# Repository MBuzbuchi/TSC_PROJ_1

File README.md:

# TSC_PROJ_1

E_Book proj

# _**Bloc Scheme**_

# _**Description of Hardware Functionality**_

Below is an extended list of the hardware components identified in the schematic, along with each component’s role and functionality, 
plus some operational details. These explanations help clarify how the entire system is built and why these design choices were made.

## 1. USB-C Connector & ESD Protection

### Key Components
- **USBLC6-2SC6Y** – TVS (Transient Voltage Suppressor) diode specialized for USB data line protection.  
  - **Approx. Price**: \$0.10–\$0.30 (single unit)  
- **PFMF.050.1** – resettable fuse (PTC) protecting the power line from excessive current.  
  - **Approx. Price**: \$0.10–\$0.20  
- **R2-USB1 / R2-USB** (5 kΩ) – matching/termination resistors on the USB D+ and D– data lines.  
  - **Approx. Price**: \$0.01–\$0.02 each  

### Function
- The USB-C connector supplies both power (5 V) to the system and USB data connectivity.  
- The ESD protection diode safeguards the USB data lines from electrostatic discharges up to several kV, maintaining the integrity of the data signals and internal converters.  
- The PTC fuse automatically resets once the current drops, preventing damage when short circuits or overcurrent situations occur on the USB port.

### Operational Data
- 5 V power supply from the USB, typically up to 500 mA (USB 2.0), or more depending on the USB-C source.  
- Data transfer rates up to 480 Mbps (USB 2.0 High Speed).

---

## 2. Voltage Regulators (LDO Voltage Regulator)

### Key Components
- **XC6220A331MR-G** – an LDO (Low Dropout) regulator delivering a stable 3.3 V output.  
  - **Approx. Price**: \$0.20–\$0.50  
- **DMG2305UX-7** – P-channel MOSFET used for power switching (possibly for reverse voltage protection or for reducing quiescent current when switching between USB and battery power).  
  - **Approx. Price**: \$0.10–\$0.30  

### Function
- Provides a constant 3.3 V rail for powering the ESP32-C6 and other logic circuits/sensors.  
- Can also serve as an additional protection stage, keeping the supply stable and filtering noise that may come from the USB source.

### Operational Data
- Input voltage range: ~3.5 V to 5.5 V (according to the LDO specs).  
- Output current up to ~300 mA.  
- Built-in overcurrent and thermal shutdown protection, ensuring circuit safety.

---

## 3. Li-Po Charging Controller (MCP73831/73832)

### Key Component
- **MCP73831** – a simple charge-management IC, configurable by an external resistor (PROG) to set the charge current.  
  - **Approx. Price**: \$0.50–\$0.80  

### Function
- Safely charges a single-cell Li-Po battery, regulating up to 4.2 V and controlling a maximum charge current.  
- Integrates temperature monitoring (via external NTC or dedicated resistor), charge status indicator (LED), and automatically switches to a float maintenance mode once the battery is fully charged.

### Operational Data
- Typically powered by a 5 V USB input.  
- Charge current (set by the PROG resistor) – e.g., 100 mA, 500 mA, etc., depending on the battery requirements.  
- Over-voltage, over-temperature, and short-circuit protection.

---

## 4. Single-Cell Li-Po Battery

### Function
- Stores electrical energy to power the device, enabling operation without a continuous USB supply.

### Operational Data
- Nominal voltage of ~3.7 V, fully charged at 4.2 V.  
- Capacity depends on the specific battery (500 mAh, 1000 mAh, etc.), which affects run time.  
- **Approx. Price**: Ranges from \$3 to \$8 or more, depending on capacity/brand.

---

## 5. ESP32-C6 Microcontroller (ESP32-C6-WROOM-1-N8)

### Function
- Core processing unit, running firmware and handling wireless communication (Wi-Fi 6, Bluetooth LE), as well as peripheral interfaces (SPI, I2C, UART, GPIO).  
- Integrates a 160 MHz RISC-V CPU, onboard Flash, SRAM, and hardware security features.

### Operational Data
- Powered at 3.3 V.  
- Low-power modes for efficient battery operation, ideal for portable IoT applications.  
- Interfaces with the E-Paper display (SPI), SD card (SPI), BME688 sensor (I2C), DS3231 RTC (I2C), and MAX17048 fuel gauge (I2C).  
- **Approx. Price**: \$2.50–\$5.00 (depending on memory size and supplier)

---

## 6. SD Card Interface

### Key Components
- MicroSD socket with card detection pins (CD, DETECTION_1, DETECTION_2).  
  - **Approx. Price**: \$0.40–\$1.00

### Function
- Provides a removable storage option for logging data, configuration files, E-Paper images, etc.  
- Uses SPI lines (SCK, MISO, MOSI, SS_SD) for communication with the ESP32-C6.

### Operational Data
- Operates at 3.3 V.  
- Supports SD/SDHC cards up to multiple GB, depending on firmware support.
- SD card itself (not included in the socket cost) can range from \$3 to \$20+ depending on capacity and speed class.

---

## 7. E-Paper Drive Circuit

### Key Components
- **MBR0530** Schottky diodes (e.g., D3, D4, D5) for protection and rectification in the voltage-boosting section.  
  - **Approx. Price**: \$0.05–\$0.10 each  
- **Inductor L1** (68 µH) for boost converter operation.  
  - **Approx. Price**: \$0.10–\$0.30 (depends on current rating)  
- **SI1308EDL-T1-GE3** MOSFET for switching in the high-voltage generator.  
  - **Approx. Price**: \$0.15–\$0.30  

### Function
- Creates the specialized positive and negative voltages (EPD_VGH, EPD_VGL) required by the E-Paper display.  
- Converts 3.3 V into higher and/or negative voltages needed to update the E-Ink display.

### Operational Data
- Typical output ranges: +15…22 V and -15…22 V (depending on the specific panel).  
- MBR0530 diodes have a low forward drop and can handle relatively high currents for this type of circuit.

---

## 8. Display Type Selector

### Key Components
- Jumper **SJ1**, resistor **R2** (2.2 kΩ).  
  - **Approx. Price**: Jumper \$0.05–\$0.10, resistor \$0.01–\$0.02

### Function
- Allows configuration of control pins (e.g. **RES**, **BUSY**) or power lines to support various E-Paper panel types.  
- Moving the jumper can route or enable certain lines depending on the display’s requirements.

---

## 9. E-Paper Display Header

### Component
- FFC (Flat Flex Cable) connector, **FH34SRJ-24S-0.5SH** (24-pin) or similar.  
  - **Approx. Price**: \$0.40–\$0.80

### Function
- A mechanical and electrical interface between the main board and the E-Paper module.  
- Includes SPI signals (SCK, MOSI, MISO—if bi-directional), control signals (CS, DC), reset line (RES), busy line (BUSY), and power lines (3.3 V, GND, EPD_VGH, EPD_VGL).

---

## 10. Battery Fuel Gauge (MAX17048)

### Key Component
- **MAX17048G+T10** – Fuel gauge with an I²C interface.  
  - **Approx. Price**: \$1.20–\$2.00

### Function
- Measures the Li-Po battery voltage and estimates its state of charge (SOC) in real time, compensating for temperature and discharge characteristics.  
- Allows the microcontroller to display battery level and react to critical low-battery states.

### Operational Data
- I²C interface at 3.3 V.  
- ±1–2% SOC accuracy.  
- Configurable alert output for low battery.

---

## 11. External Flash Memory (W25Q512JVEIQ, 64MB)

### Function
- Additional non-volatile storage (up to 64Mb or 512Mbit, i.e. 8 MB, depending on suffix) for images, fonts, configuration files, and Over-the-Air (OTA) firmware updates.

### Operational Data
- SPI interface with speeds up to 133 MHz.  
- 3.3 V supply voltage.  
- Up to 100,000 write/erase cycles and 20-year data retention.  
- **Approx. Price**: \$1.50–\$3.00 (depending on density and supplier)

---

## 12. SPI ESD Protection Lines

### Key Components
- **PGB1010603MR** (Polymeric ESD Suppressor) and 10 kΩ series resistors.  
  - **Approx. Price**: \$0.05–\$0.15 each for the suppressors, \$0.01 for each resistor

### Function
- Protects SPI data lines from electrostatic discharges, which can occur when plugging in peripherals or when the lines are touched without proper handling.  
- The 10 kΩ resistors help limit transient current before it reaches the TVS diode, providing additional filtering.

### Operational Data
- ESD protection up to ±8 kV (contact discharge).

---

## 13. Qwiic / Stemma QT Connector (I2C)

### Component
- 4-pin connector (GND, 3.3 V, SDA, SCL).  
  - **Approx. Price**: \$0.30–\$0.60

### Function
- Provides a standardized, plug-and-play interface for quickly adding I2C-based sensors or other modules.

### Operational Data
- Compatible with SparkFun Qwiic and Adafruit Stemma QT systems.  
- 3.3 V supply voltage.

---

## 14. RTC Module (DS3231SN)

### Key Component
- **DS3231SN** – A high-accuracy real-time clock with an integrated temperature-compensated oscillator (TCXO).  
  - **Approx. Price**: \$1.50–\$3.00

### Function
- Maintains precise timekeeping with minimal drift (±2 ppm, equivalent to ±1 minute/year in some conditions).  
- Communicates with the microcontroller via I²C for automatic time syncing.  
- Can keep time even when main power is off, using a backup battery on VBAT.

### Operational Data
- 3.3 V supply voltage.  
- Operating temperature range from -40 °C to +85 °C (depending on the specific version).

---

## 15. Test Pads

### Component
- Test points (TP1…TP17) placed around the PCB.  
  - **Approx. Price**: Usually negligible (just copper pads), sometimes \$0.01–\$0.02 each if you count plating cost.

### Function
- Provide direct access to key signals (SPI, I2C, GPIO) for debugging, measurements, programming, or firmware updates.  
- Highly useful for prototyping, quality control, and mass production validation.

---

# _**Bill of Materials**_
Data sheets and links to websites were included only at the first mention of components that appear multiple times in the project. Components such as test points (TP), do not have tehnical description or present a data sheet because these were designed personally

| Name of component  | Device                                    | Check Prices                                                                 | DataSheet                                                                  |
|--------------------|-------------------------------------------|-----------------------------------------------------------------------------|----------------------------------------------------------------------------|
| BOOT_BUTTON        | BUTTON_CUSYOMV1                           | [Check Price](https://industry.panasonic.com/global/en/products/control/switch/light-touch/number/evqpuj02k)  | [DataSheet](https://industry.panasonic.com/global/en/products/control/switch/light-touch/number/evqpuj02k) |
| C1                 | ESP32_WROVER_EAGLE-LTSPICE_CC0402         | [Check Price](https://industry.panasonic.com/global/en/products/control/switch/light-touch/number/evqpuj02k)  | [DataSheet](https://industry.panasonic.com/global/en/products/control/switch/light-touch/number/evqpuj02k) |
| C1_BAT             | ESP32_WROVER_EAGLE-LTSPICE_CC0402         | #N/A                                                                         | #N/A                                                                      |
| C1_BAT1            | EAGLE-LTSPICE_CC0402                      | #N/A                                                                         | #N/A                                                                      |
| C1_BAT2            | EAGLE-LTSPICE_CC0402                      | #N/A                                                                         | #N/A                                                                      |
| C2                 | ESP32_WROVER_EAGLE-LTSPICE_CC0402         | #N/A                                                                         | #N/A                                                                      |
| C2_BAT\            | ESP32_WROVER_EAGLE-LTSPICE_CC0402         | #N/A                                                                         | #N/A                                                                      |
| C3                 | RCL_CPOL-EUCT3528                         | #N/A                                                                         | #N/A                                                                      |
| C4                 | ESP32_WROVER_EAGLE-LTSPICE_CC0402         | #N/A                                                                         | #N/A                                                                      |
| C4_USB             | ESP32_WROVER_EAGLE-LTSPICE_CC0402         | #N/A                                                                         | #N/A                                                                      |
| C5                 | ESP32_WROVER_EAGLE-LTSPICE_CC0402         | #N/A                                                                         | #N/A                                                                      |
| C5_USB             | ESP32_WROVER_EAGLE-LTSPICE_CC0402         | #N/A                                                                         | #N/A                                                                      |
| C6                 | ESP32_WROVER_EAGLE-LTSPICE_CC0402         | #N/A                                                                         | #N/A                                                                      |
| C7                 | ESP32_WROVER_EAGLE-LTSPICE_CC0402         | #N/A                                                                         | #N/A                                                                      |
| C8                 | ESP32_WROVER_EAGLE-LTSPICE_CC0402         | #N/A                                                                         | #N/A                                                                      |
| C9                 | EAGLE-LTSPICE_CC0402                      | #N/A                                                                         | #N/A                                                                      |
| C10                | ESP32_WROVER_EAGLE-LTSPICE_CC0402         | #N/A                                                                         | #N/A                                                                      |
| C10_SUPERCAP       | CPH3225A                                  | [Check Price](https://www.snapeda.com/parts/CPH3225A/Seiko+Instruments/view-part/?ref=eda) | [DataSheet](https://www.snapeda.com/parts/CPH3225A/Seiko+Instruments/view-part/?ref=eda) |
| CHANGE_BUTTON      | BUTTON_CUSYOMV1                           | [Check Price](https://industry.panasonic.com/global/en/products/control/switch-light-touch/number/evqpuj02k)  | [DataSheet](https://industry.panasonic.com/global/en/products/control/switch-light-touch/number/evqpuj02k) |
| CHG_LED            | ADAFRUIT_LEDCHIP-LED0603                  | [Check Price](https://www.snapeda.com/parts/KP-1608SURCK/Kingbright/view-part/?ref=search&t=LED%200603) | [DataSheet](https://www.snapeda.com/parts/KP-1608SURCK/Kingbright/view-part/?ref=search&t=LED%200603) |
| C_DELAY            | ESP32_WROVER_EAGLE-LTSPICE_CC0402         | #N/A                                                                         | #N/A                                                                      |
| D1                 | USBLC6-2SC6Y                              | [Check Price](https://www.snapeda.com/parts/USBLC6-2SC6Y/STMicroelectronics/view-part/?ref=eda) | [DataSheet](https://www.snapeda.com/parts/USBLC6-2SC6Y/STMicroelectronics/view-part/?ref=eda) |
| D2                 | ESP32_WROVER_AVX---SD0805S020S1R0_AVX_... | [Check Price](https://eu.mouser.com/ProductDetail/KYOCERA-AVX/SD0805S020S1R0?qs=jCA%252BPfw4LHbpkAoSnwrdjw%3D%3D) | [DataSheet](http://datasheets.avx.com/schottky.pdf)                       |
| D3                 | MBR0530                                   | [Check Price](https://eu.mouser.com/ProductDetail/KYOCERA-AVX/SD0805S020S1R0?qs=jCA%252BPfw4LHbpkAoSnwrdjw%3D%3D) | [DataSheet](https://eu.mouser.com/ProductDetail/KYOCERA-AVX/SD0805S020S1R0?qs=jCA%252BPfw4LHbpkAoSnwrdjw%3D%3D) |
| D4                 | MBR0530                                   | [Check Price](https://www.snapeda.com/parts/MBR0530/Onsemi/view-part/?ref=eda) | [DataSheet](https://www.snapeda.com/parts/MBR0530/Onsemi/view-part/?ref=eda) |
| D5                 | MBR0530                                   | [Check Price](https://www.snapeda.com/parts/MBR0530/Onsemi/view-part/?ref=eda) | [DataSheet](https://www.snapeda.com/parts/MBR0530/Onsemi/view-part/?ref=eda) |
| D6                 | PGB1010603MR                              | [Check Price](https://www.snapeda.com/parts/PGB1010603MR/Littelfuse/view-part/?ref=eda) | [DataSheet](https://www.snapeda.com/parts/PGB1010603MR/Littelfuse/view-part/?ref=eda) |
| D7                 | ESP32_WROVER_AVX---SD0805S020S1R0_AVX_... | [Check Price](https://eu.mouser.com/ProductDetail/KYOCERA-AVX/SD0805S020S1R0?qs=jCA%252BPfw4LHbpkAoSnwrdjw%3D%3D) | [DataSheet](http://datasheets.avx.com/schottky.pdf)                       |
| D8                 | PGB1010603MR                              | [Check Price](https://www.snapeda.com/parts/PGB1010603MR/Littelfuse/view-part/?ref=eda) | [DataSheet](https://www.snapeda.com/parts/PGB1010603MR/Littelfuse/view-part/?ref=eda) |
| D9                 | PGB1010603MR                              | [Check Price](https://www.snapeda.com/parts/PGB1010603MR/Littelfuse/view-part/?ref=eda) | [DataSheet](https://www.snapeda.com/parts/PGB1010603MR/Littelfuse/view-part/?ref=eda) |
| D10                | PGB1010603MR                              | [Check Price](https://www.snapeda.com/parts/PGB1010603MR/Littelfuse/view-part/?ref=eda) | [DataSheet](https://www.snapeda.com/parts/PGB1010603MR/Littelfuse/view-part/?ref=eda) |
| D11                | PGB1010603MR                              | [Check Price](https://www.snapeda.com/parts/PGB1010603MR/Littelfuse/view-part/?ref=eda) | [DataSheet](https://www.snapeda.com/parts/PGB1010603MR/Littelfuse/view-part/?ref=eda) |
| D12                | PGB1010603MR                              | [Check Price](https://www.snapeda.com/parts/PGB1010603MR/Littelfuse/view-part/?ref=eda) | [DataSheet](https://www.snapeda.com/parts/PGB1010603MR/Littelfuse/view-part/?ref=eda) |
| EPD_C1             | ESP32_WROVER_EAGLE-LTSPICE_CC0402         | #N/A                                                                         | #N/A                                                                      |
| EPD_C2             | ESP32_WROVER_EAGLE-LTSPICE_CC0402         | #N/A                                                                         | #N/A                                                                      |
| EPD_C5             | ESP32_WROVER_EAGLE-LTSPICE_CC0402         | #N/A                                                                         | #N/A                                                                      |
| EPD_C6             | ESP32_WROVER_EAGLE-LTSPICE_CC0402         | #N/A                                                                         | #N/A                                                                      |
| EPD_C7             | ESP32_WROVER_EAGLE-LTSPICE_CC0402         | #N/A                                                                         | #N/A                                                                      |
| EPD_C8             | ESP32_WROVER_EAGLE-LTSPICE_CC0402         | #N/A                                                                         | #N/A                                                                      |
| EPD_C9             | ESP32_WROVER_EAGLE-LTSPICE_CC0402         | #N/A                                                                         | #N/A                                                                      |
| EPD_C10            | ESP32_WROVER_EAGLE-LTSPICE_CC0402         | #N/A                                                                         | #N/A                                                                      |
| EPD_C11            | ESP32_WROVER_EAGLE-LTSPICE_CC0402         | #N/A                                                                         | #N/A                                                                      |
| EPD_C12            | ESP32_WROVER_EAGLE-LTSPICE_CC0402         | #N/A                                                                         | #N/A                                                                      |
| IC1                | BD5229G-TR                                | [Check Price](https://componentsearchengine.com/part-view/BD5229G-TR/ROHM%20Semiconductor) | [DataSheet](https://componentsearchengine.com/part-view/BD5229G-TR/ROHM%20Semiconductor) |
| IC4                | XC6220A331MR-G                            | [Check Price](https://componentsearchengine.com/part-view/XC6220A331MR-G/Torex) | [DataSheet](https://componentsearchengine.com/part-view/XC6220A331MR-G/Torex) |
| J1                 | FH34SRJ-24S-0.5SH_99_                     | [Check Price](https://componentsearchengine.com/part-view/XC6220A331MR-G/Torex) | [DataSheet](https://componentsearchengine.com/part-view/XC6220A331MR-G/Torex) |
| J2                 | SAMACSYS_PARTS_USB4110-GF-A               | [Check Price](https://componentsearchengine.com/part-view/USB4110-GF-A/GCT%20(GLOBAL%20CONNECTOR%20TECHNOLOGY) | [DataSheet](https://componentsearchengine.com/part-view/USB4110-GF-A/GCT%20(GLOBAL%20CONNECTOR%20TECHNOLOGY) |
| J3                 | QWIIC_CONNECTORJS-1MM                     | #N/A                                                                         | #N/A                                                                      |
| J4                 | 112A-TAAR-R03_ATTEND                      | [Check Price](https://store.comet.srl.ro/Catalogue/Product/43497/)           | [DataSheet](https://store.comet.srl.ro/Catalogue/Product/43497/)          |
| L1                 | 744043680IND_4828-WE-TPC_WRE              | [Check Price](https://eu.mouser.com/ProductDetail/Wurth-Elektronik/744043680?qs=PGXP4M47uW6VkZq%252BkzjrHA%3D%3D) | [DataSheet](https://eu.mouser.com/ProductDetail/Wurth-Elektronik/744043680?qs=PGXP4M47uW6VkZq%252BkzjrHA%3D%3D) |
| PFMF.050.1         | ESP32C6_VARISTORCN1812                    | [Check Price](https://www.mouser.co.uk/ProductDetail/EPCOS-TDK/B72520T0350K062?qs=dEfas%2FXlABIszF52uu7vrg%3D%3D) | [DataSheet](https://www.mouser.co.uk/ProductDetail/EPCOS-TDK/B72520T0350K062?qs=dEfas%2FXlABIszF52uu7vrg%3D%3D) |
| Q1                 | ESP32_WROVER_SPARKFUN-DISCRETESEMI_MOSFET_... | [Check Price](https://componentsearchengine.com/part-view/DMG2305UX-7/Diodes%20Incorporated) | [DataSheet](https://componentsearchengine.com/part-view/DMG2305UX-7/Diodes%20Incorporated) |
| Q2                 | ESP32_WROVER_SPARKFUN-DISCRETESEMI_MOSFET_... | #N/A                                                                         | #N/A                                                                      |
| Q3                 | D8                                        | [Check Price](https://componentsearchengine.com/part-view/PGB1010603MR/Littelfuse) | [DataSheet](https://componentsearchengine.com/part-view/PGB1010603MR/Littelfuse) |
| Q4                 | Q2_TS-B2_REACHPACK                        | #N/A                                                                         | #N/A                                                                      |

# _**Pin Allocation for ESP32-C6**_

| Pin ESP32-C6  | Componentă / Semnal                       | Explicație                                           |
|---------------|-------------------------------------------|------------------------------------------------------|
| GPIO1         | I²C SDA (BME688, MAX17048, DS3231, Qwiic) | Se folosește pentru a partaja magistrala I²C între toți senzorii și RTC. |
| GPIO2         | I²C SCL (BME688, MAX17048, DS3231, Qwiic) | Linia de clock pentru comunicarea I²C.              |
| GPIO5         | SPI MISO (E-Paper)                       | Pinul pentru citirea datelor sau a statusului de la ecranul e-paper. |
| GPIO6         | SPI MOSI (E-Paper)                       | Trimiterea datelor către ecranul e-paper.            |
| GPIO7         | SPI CLK (E-Paper)                        | Semnal de clock pentru sincronizarea cu e-paper.    |
| GPIO8         | SPI CS (E-Paper)                         | Chip Select pentru a activa comunicarea cu e-paper.  |
| GPIO9         | E-Paper DC (Data/Command)                | Semnal pentru a diferenția între date și comenzi pentru ecranul e-paper. |
| GPIO10        | E-Paper RST                              | Pinul de reset hardware pentru e-paper.              |
| GPIO11        | E-Paper BUSY                             | Intrare din display care indică dacă ecranul este ocupat sau nu. |
| GPIO12        | Button #1                                | Intrare digitală pentru primul buton (ex. pagina următoare). |
| GPIO13        | Button #2                                | Intrare digitală pentru al doilea buton (ex. pagina anterioară). |
| GPIO14        | Button #3                                | Intrare digitală pentru al treilea buton (ex. Meniu/OK). |
| GPIO15        | MAX17048 ALERT (opțional)                | Semnal de alertă de la MAX17048 pentru nivel scăzut al bateriei. |
| GPIO16        | USB D+ (intern la USB PHY)               | Pin dedicat pentru semnalul USB 2.0 (D+).            |
| GPIO17        | USB D- (intern la USB PHY)               | Pin dedicat pentru semnalul USB 2.0 (D-).            |
| GPIO18        | LED de status (opțional)                 | Indicator pentru diverse stări (ex. Wi-Fi, încărcare, etc.). |
| GPIO19        | SD Card CS (opțional)                    | Chip Select pentru cardul SD (dacă se folosește SPI). |
| GPIO20        | SD Card MISO (opțional)                  | Intrare date de la cardul SD.                        |
| GPIO21        | SD Card MOSI (opțional)                  | Ieșire date către cardul SD.                         |
| GPIO4         | SD Card CLK (opțional)                   | Semnal de clock pentru cardul SD (SPI).              |

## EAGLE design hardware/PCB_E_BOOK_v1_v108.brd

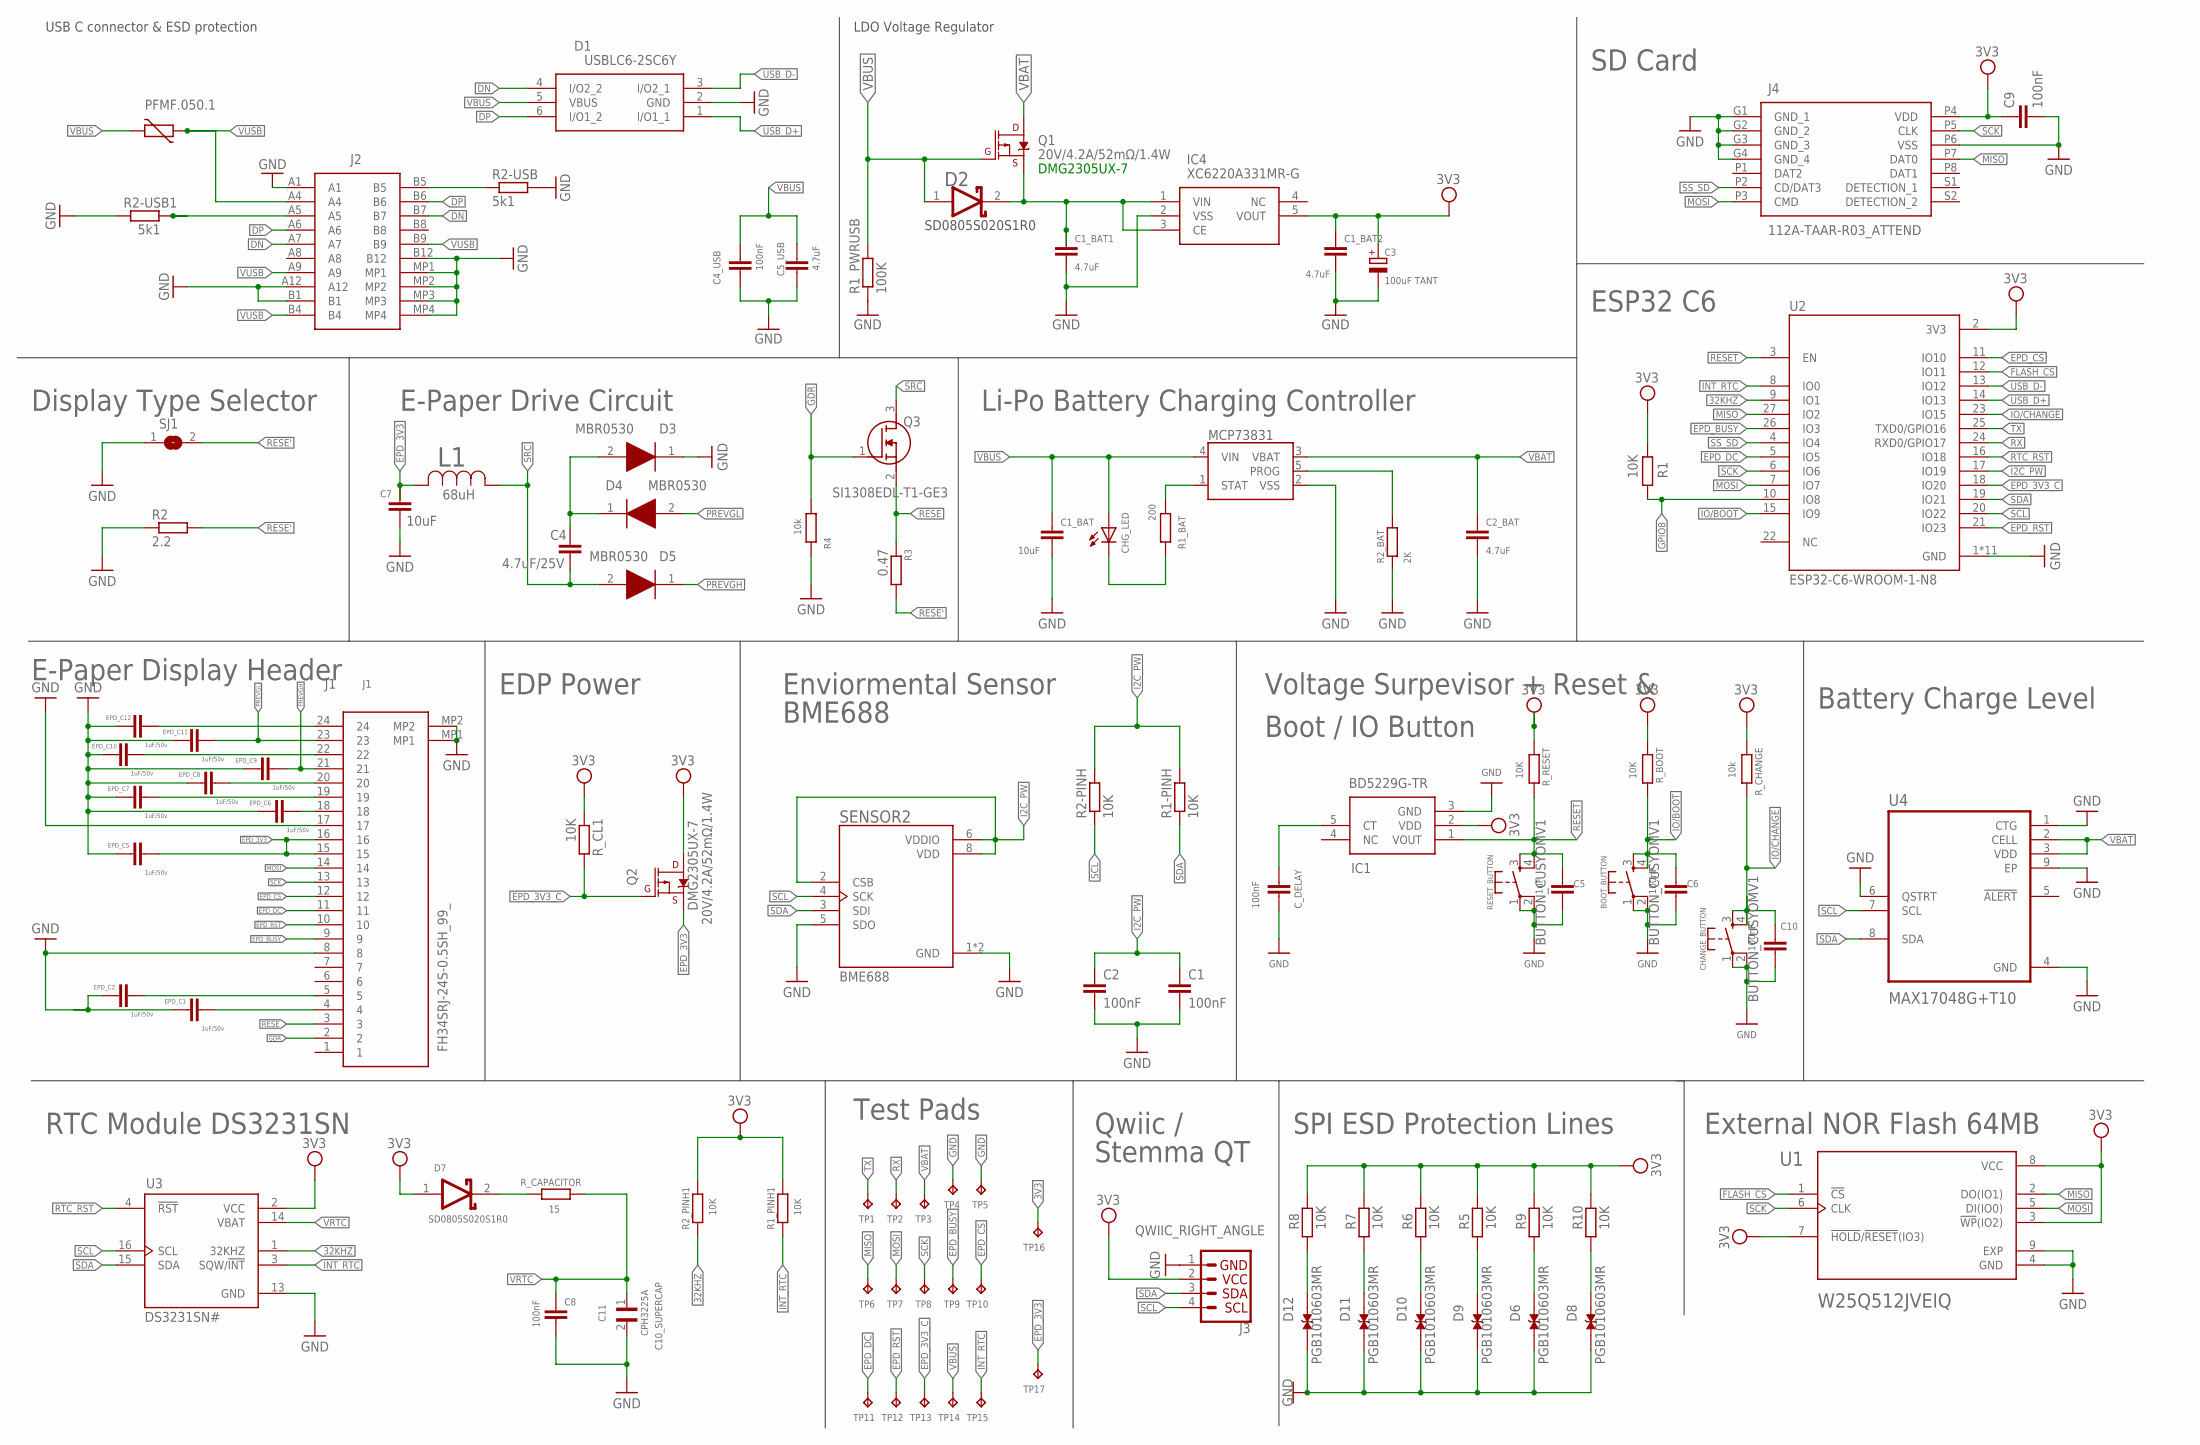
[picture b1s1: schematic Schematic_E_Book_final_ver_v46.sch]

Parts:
BOOT_BUTTON: BUTTON_CUSYOMV1; MYBUTTON
C1, C2, C4_USB, C6, C8, C9, C10: 100nF; EAGLE-LTSPICE_C0402
C1_BAT, C7: 10uF; EAGLE-LTSPICE_C0402
C1_BAT1, C1_BAT2, C2_BAT, C5_USB: 4.7uF; EAGLE-LTSPICE_C0402
C3: 100uF TANT; RCL_CT3528
C4: 4.7uF/25V; EAGLE-LTSPICE_C0402
C5: 1uF; EAGLE-LTSPICE_C0402
C11: CPH3225A; CAPCP3225X100N
CHANGE_BUTTON: BUTTON_CUSYOMV1; MYBUTTON
CHG_LED: ADAFRUIT_LEDCHIP-LED0603; ADAFRUIT_CHIP-LED0603
C_DELAY: 100nF; EAGLE-LTSPICE_C0402
D1: USBLC6-2SC6Y; SOT95P280X145-6N
D2: SD0805S020S1R0; ESP32_WROVER_AVX---SD0805S020S1R0_AVX_SD0805S020S1R0_0
D3, D4, D5: MBR0530; SOD3716X135N
D6, D8, D9, D10, D11, D12: PGB1010603MR; DIOC1608X36N
D7: ESP32_WROVER_AVX---SD0805S020S1R0_AVX_SD0805S020S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; ESP32_WROVER_AVX---SD0805S020S1R0_AVX_SD0805S020S1R0_0
EPD_C1, EPD_C2, EPD_C5, EPD_C6, EPD_C7, EPD_C8, EPD_C9, EPD_C10, EPD_C11, EPD_C12: 1uF/50v; EAGLE-LTSPICE_C0402
IC1: BD5229G-TR; SOT95P280X125-5N
IC4: XC6220A331MR-G; SOT95P280X120-5N
J1: FH34SRJ-24S-0.5SH_99_; FH34SRJ24S05SH99
J2: SAMACSYS_PARTS_USB4110-GF-A; SAMACSYS_PARTS_USB4110GFA
J3: QWIIC_RIGHT_ANGLE; JST04_1MM_RA
J4: 112A-TAAR-R03_ATTEND; 112ATAARR03ATTEND
L1: 68uH; IND_4828-WE-TPC_WRE
MCP73831: ESP32_WROVER_SPARKFUN-IC-POWER_MCP73831; ESP32_WROVER_SPARKFUN-IC-POWER_SOT23-5
PFMF.050.1: ESP32C6_VARISTORCN1812; ESP32C6_VARISTOR_CT/CN1812
Q1, Q2: 20V/4.2A/52mΩ/1.4W; ESP32_WROVER_SPARKFUN-DISCRETESEMI_SOT23-3
Q3: SI1308EDL-T1-GE3; SOT65P210X110-3N
R1, R1-PINH, R1_PINH1, R2-PINH, R2_PINH1, R5, R6, R7, R8, R9, R10: 10K; ESP32_WROVER_EAGLE-LTSPICE_R0402
R1_BAT: 200; ESP32_WROVER_EAGLE-LTSPICE_R0402
R1_PWRUSB: 100K; ESP32_WROVER_EAGLE-LTSPICE_R0402
R2: 2.2; ESP32_WROVER_EAGLE-LTSPICE_R0402
R2-USB, R2-USB1: 5k1; ESP32_WROVER_EAGLE-LTSPICE_R0402
R2_BAT: 2K; ESP32_WROVER_EAGLE-LTSPICE_R0402
R3: 0.47; ESP32_WROVER_EAGLE-LTSPICE_R0402
R4: 10k; ESP32_WROVER_EAGLE-LTSPICE_R0402
RESET_BUTTON: BUTTON_CUSYOMV1; MYBUTTON
R_BOOT: 10K; ESP32_WROVER_EAGLE-LTSPICE_R0402
R_CAPACITOR: 15; ESP32_WROVER_EAGLE-LTSPICE_R0402
R_CHANGE: 10k; ESP32_WROVER_EAGLE-LTSPICE_R0402
R_CL1: 10K; ESP32_WROVER_EAGLE-LTSPICE_R0402
R_RESET: 10K; ESP32_WROVER_EAGLE-LTSPICE_R0402
SENSOR2: ESP32_WROVER_BME680_BME680; ESP32_WROVER_BME680_PSON80P300X300X100-8N
SJ1: SJ
TP1, TP2, TP3, TP4, TP5, TP6, TP7, TP8, TP9, TP10, TP11, TP12, TP13, TP14, TP15, TP16, TP17: TPTP20R; TP20R
U1: W25Q512JVEIQ; SON127P600X800X80-9N
U2: ESP32-C6-WROOM-1-N8; XCVR_ESP32-C6-WROOM-1-N8
U3: DS3231SN#; SOIC127P1032X265-16N
U4: MAX17048G+T10; SON50P200X200X80-9N

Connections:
3V3: C1_BAT2.1, C3.+, C9.1, D7.1 (ANODE), IC1.2 (VDD), IC4.5 (VOUT), J3.2, J4.P4 (VDD), Q2.3 (D), R1.2, R1_PINH1.2, R2_PINH1.2, R5.2, R6.2, R7.2, R8.2, R9.2, R10.2, R_BOOT.1, R_CHANGE.1, R_CL1.1, R_RESET.1, TP16.TP, U1.3 (!WP!(IO2)), U1.7 (!HOLD!/!RESET!(IO3)), U1.8 (VCC), U2.2 (3V3), U3.2 (VCC)
32KHZ: R2_PINH1.1, U2.9 (IO1), U3.1 (32KHZ)
DN: D1.4 (I/O2_2), J2.A7, J2.B7
DP: D1.6 (I/O1_2), J2.A6, J2.B6
EPD_3V3: C7.1, EPD_C5.1, J1.15, J1.16, L1.2, Q2.2 (S), TP17.TP
EPD_3V3_C: Q2.1 (G), R_CL1.2, TP13.TP, U2.18 (IO20)
EPD_BUSY: J1.9, TP9.TP, U2.26 (IO3)
EPD_CS: J1.12, TP10.TP, U2.11 (IO10)
EPD_DC: J1.11, TP11.TP, U2.5 (IO5)
EPD_RST: J1.10, TP12.TP, U2.21 (IO23)
FLASH_CS: U1.1 (!CS), U2.12 (IO11)
GDR: J1.2, Q3.1 (G), R4.2
GND: BOOT_BUTTON.1, BOOT_BUTTON.2, C1.2, C1_BAT.2, C1_BAT1.2, C1_BAT2.2, C2.2, C2_BAT.2, C3.-, C4_USB.2, C5.2, C5_USB.2, C6.2, C7.2, C8.2, C9.2, C10.2, C11.2, CHANGE_BUTTON.1, CHANGE_BUTTON.2, C_DELAY.2, D1.2 (GND), D3.1 (K), D6.1, D8.1, D9.1, D10.1, D11.1, D12.1, EPD_C1.2, EPD_C2.2, EPD_C5.2, EPD_C6.2, EPD_C7.2, EPD_C8.2, EPD_C9.2, EPD_C10.2, EPD_C11.2, EPD_C12.2, IC1.3 (GND), IC4.2 (VSS), J1.8, J1.17, J1.MP1, J1.MP2, J2.A1, J2.A12, J2.B1, J2.B12, J2.MP1, J2.MP2, J2.MP3, J2.MP4, J3.1, J4.G1 (GND_1), J4.G2 (GND_2), J4.G3 (GND_3), J4.G4 (GND_4), J4.P6 (VSS), MCP73831.2 (VSS), R1_PWRUSB.1, R2.1, R2-USB.2, R2-USB1.1, R2_BAT.1, R4.1, RESET_BUTTON.1, RESET_BUTTON.2, SENSOR2.1 (GND), SENSOR2.5 (SDO), SENSOR2.7 (GND), SJ1.1, TP4.TP, TP5.TP, U1.4 (GND), U1.9 (EXP), U2.1 (GND), U2.28 (GND), U2.29_1 (GND), U2.29_2 (GND), U2.29_3 (GND), U2.29_4 (GND), U2.29_5 (GND), U2.29_6 (GND), U2.29_7 (GND), U2.29_8 (GND), U2.29_9 (GND), U3.13 (GND), U4.1 (CTG), U4.4 (GND), U4.6 (QSTRT), U4.9 (EP)
GPIO8: R1.1, U2.10 (IO8)
I2C_PW: C1.1, C2.1, R1-PINH.2, R2-PINH.2, SENSOR2.2 (CSB), SENSOR2.6 (VDDIO), SENSOR2.8 (VDD), U2.17 (IO19)
INT_RTC: R1_PINH1.1, TP15.TP, U2.8 (IO0), U3.3 (SQW/!INT)
IO/BOOT: BOOT_BUTTON.3, BOOT_BUTTON.4, C6.1, R_BOOT.2, U2.15 (IO9)
IO/CHANGE: C10.1, CHANGE_BUTTON.3, CHANGE_BUTTON.4, R_CHANGE.2, U2.23 (IO15)
MISO: J4.P7 (DAT0), TP6.TP, U1.2 (DO(IO1)), U2.27 (IO2)
MOSI: J1.14, J4.P3 (CMD), TP7.TP, U1.5 (DI(IO0)), U2.7 (IO7)
unnamed: J2.A5, R2-USB1.2
unnamed: C1_BAT1.1, D2.2 (CATHODE), IC4.1 (VIN), IC4.3 (CE), Q1.2 (S)
unnamed: MCP73831.1 (STAT), R1_BAT.2
unnamed: MCP73831.5 (PROG), R2_BAT.2
unnamed: J2.B5, R2-USB.1
unnamed: CHG_LED.C, R1_BAT.1
unnamed: C4.1, D3.2 (A), D4.1 (K)
unnamed: D12.2, R8.1
unnamed: D11.2, R7.1
unnamed: D10.2, R6.1
unnamed: D9.2, R5.1
unnamed: D6.2, R9.1
unnamed: D8.2, R10.1
unnamed: C_DELAY.1, IC1.5 (CT)
unnamed: D7.2 (CATHODE), R_CAPACITOR.1
unnamed: EPD_C2.1, J1.5
unnamed: EPD_C1.1, J1.4
PREVGH: D5.1 (K), EPD_C9.1, J1.21
PREVGL: D4.2 (A), EPD_C11.1, J1.23
RESE: J1.3, Q3.2 (S), R3.1
RESE': R2.2, R3.2, SJ1.2
RESET: C5.1, IC1.1 (VOUT), RESET_BUTTON.3, RESET_BUTTON.4, R_RESET.2, U2.3 (EN)
RTC_RST: U2.16 (IO18), U3.4 (!RST)
RX: TP2.TP, U2.24 (RXD0/GPIO17)
SCK: J1.13, J4.P5 (CLK), TP8.TP, U1.6 (CLK), U2.6 (IO6)
SCL: J3.4, R2-PINH.1, SENSOR2.4 (SCK), U2.20 (IO22), U3.16 (SCL), U4.7 (SCL)
SDA: J3.3, R1-PINH.1, SENSOR2.3 (SDI), U2.19 (IO21), U3.15 (SDA), U4.8 (SDA)
SRC: C4.2, D5.2 (A), L1.1, Q3.3 (D)
SS_SD: J4.P2 (CD/DAT3), U2.4 (IO4)
TX: TP1.TP, U2.25 (TXD0/GPIO16)
USB_D+: D1.1 (I/O1_1), U2.14 (IO13)
USB_D-: D1.3 (I/O2_1), U2.13 (IO12)
VBAT: C2_BAT.1, MCP73831.3 (VBAT), Q1.3 (D), TP3.TP, U4.2 (CELL), U4.3 (VDD)
VBUS: C1_BAT.1, C4_USB.1, C5_USB.1, CHG_LED.A, D1.5 (VBUS), D2.1 (ANODE), MCP73831.4 (VIN), PFMF.050.1.2, Q1.1 (G), R1_PWRUSB.2, TP14.TP
VRTC: C8.1, C11.1, R_CAPACITOR.2, U3.14 (VBAT)
VRTC1: EPD_C12.1, J1.24
VRTC4: EPD_C8.1, J1.20
VRTC5: EPD_C7.1, J1.19
VRTC6: EPD_C6.1, J1.18
VRTC7: EPD_C10.1, J1.22
VUSB: J2.A4, J2.A9, J2.B4, J2.B9, PFMF.050.1.1

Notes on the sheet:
USB C connector & ESD protection
SD0805S020S1R0
DMG2305UX-7
LDO Voltage Regulator
SD Card
ESP32 C6
Li-Po Battery Charging Controller
E-Paper Drive Circuit
Display Type Selector
EDP Power
Battery Charge Level
External NOR Flash 64MB
SPI ESD Protection Lines
Qwiic /
Stemma QT
Test Pads
BME688
Enviormental Sensor
BME688
Voltage Surpevisor + Reset &
Boot / IO Button
RTC Module DS3231SN
C10_SUPERCAP
E-Paper Display Header
68uH

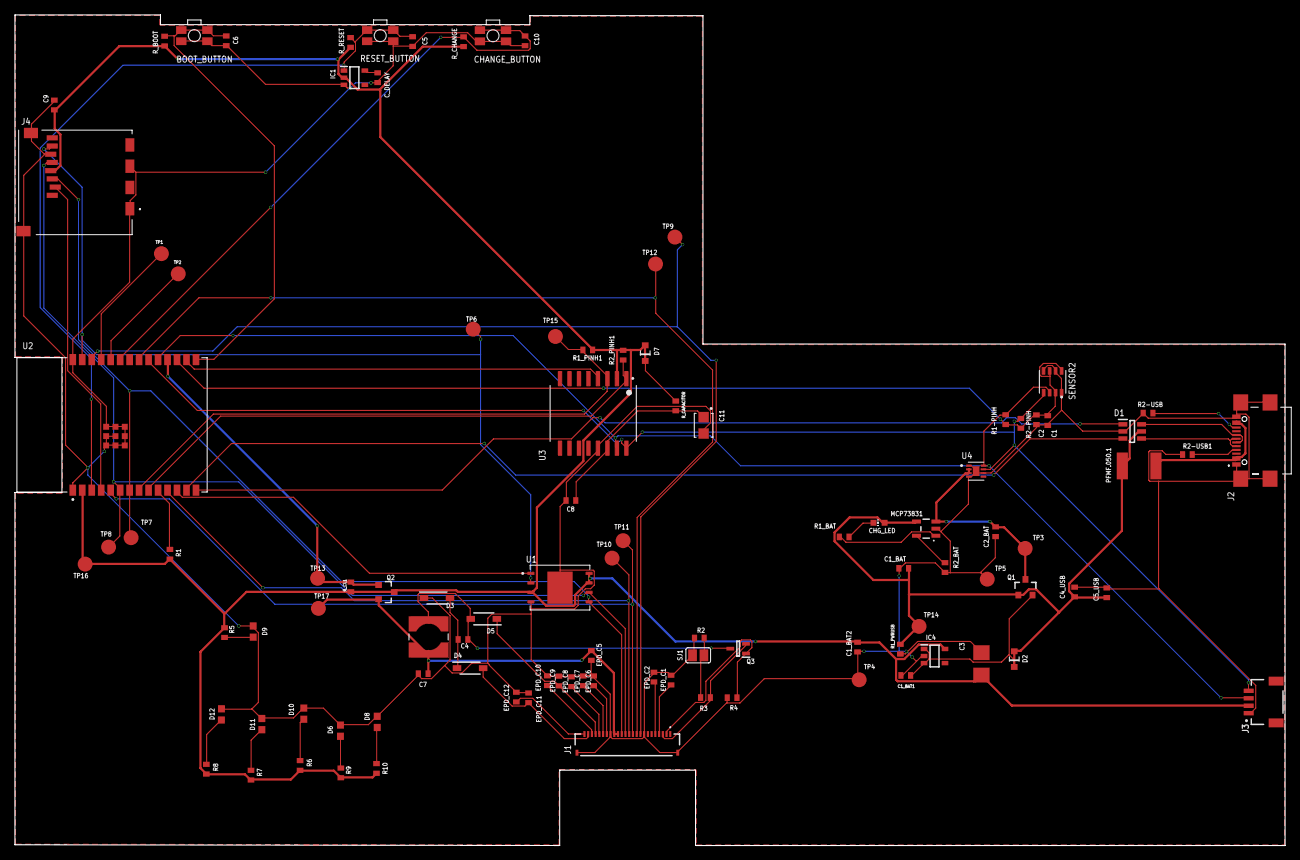
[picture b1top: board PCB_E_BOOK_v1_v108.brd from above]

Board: 2 copper layers, 170.2 x 111.3 mm, 103 parts (0 on the bottom side), 61 nets.
